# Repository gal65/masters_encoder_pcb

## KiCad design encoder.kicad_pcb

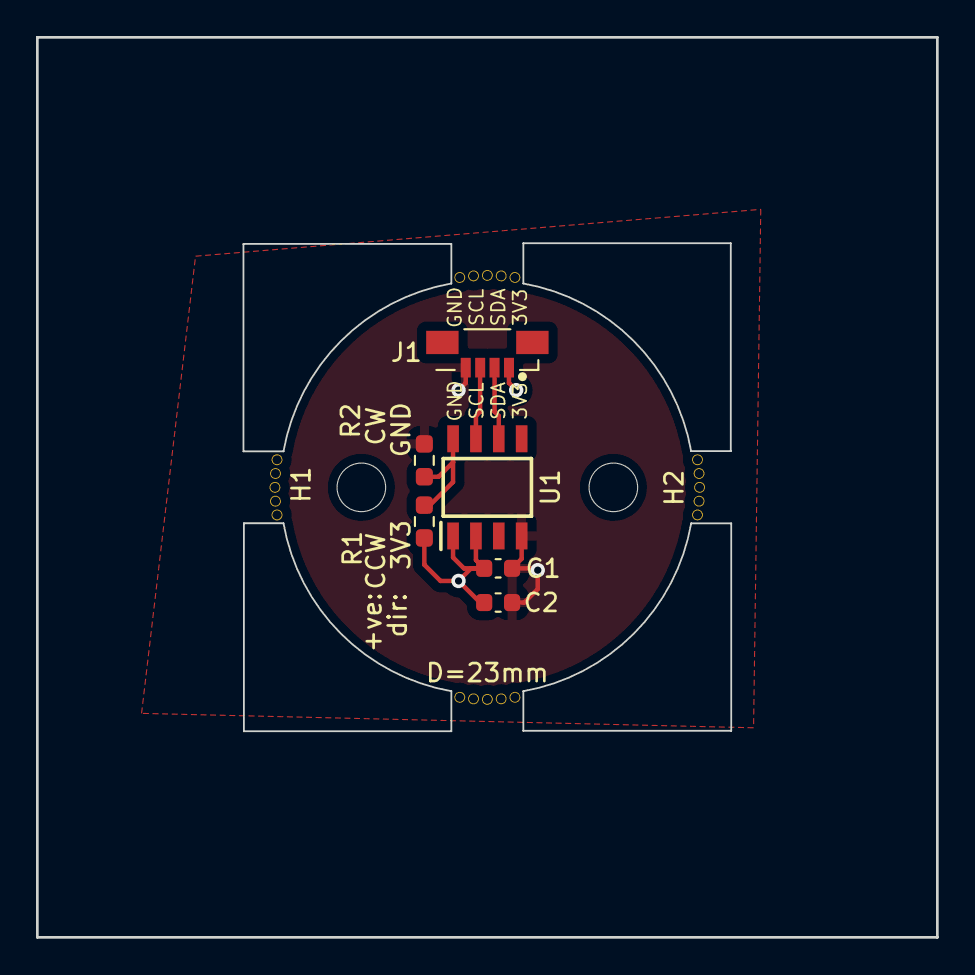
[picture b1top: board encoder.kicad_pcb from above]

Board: 2 copper layers, 50.0 x 50.0 mm, 8 parts (0 on the bottom side), 5 nets.

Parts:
C1: 100nF; C_0603_1608Metric
C2: 10uF; C_0603_1608Metric
H1, H2: MountingHole; MountingHole_2.7mm_M2.5_ISO7380
J1: BM04B-SURS-TFLFSN
R1, R2: R; R_0603_1608Metric_Pad0.98x0.95mm_HandSolder
U1: AS5600-ASOT; SOIC127P600X175-8N

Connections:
+3.3V: C1.1, C2.2, J1.1 (VDD), R1.2, U1.1 (VDD5V), U1.2 (VDD3V3)
/DIR: R1.1, R2.1, U1.8 (DIR)
/SCL: J1.3 (SCL), U1.7 (SCL)
/SDA: J1.2 (GND), U1.6 (SDA)
GND: C1.2, C2.1, J1.4 (SDA), R2.2, U1.4 (GND)

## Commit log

2022-08-22 Reworked lots
2022-09-22 changed mounting hole size from M2.5 (D2.7) to D2.1
2022-09-29 HD2.1mm, final design for production
2022-09-30 made some changes :)
2022-09-30 removed H3, regenrated gerber and drill files
2022-09-30 added frame
2022-09-30 updated gerber/drill files
2022-11-01 gigvkhkhnk
2023-02-22 BOM and fixed pcb
2023-02-23 schematic tweak
